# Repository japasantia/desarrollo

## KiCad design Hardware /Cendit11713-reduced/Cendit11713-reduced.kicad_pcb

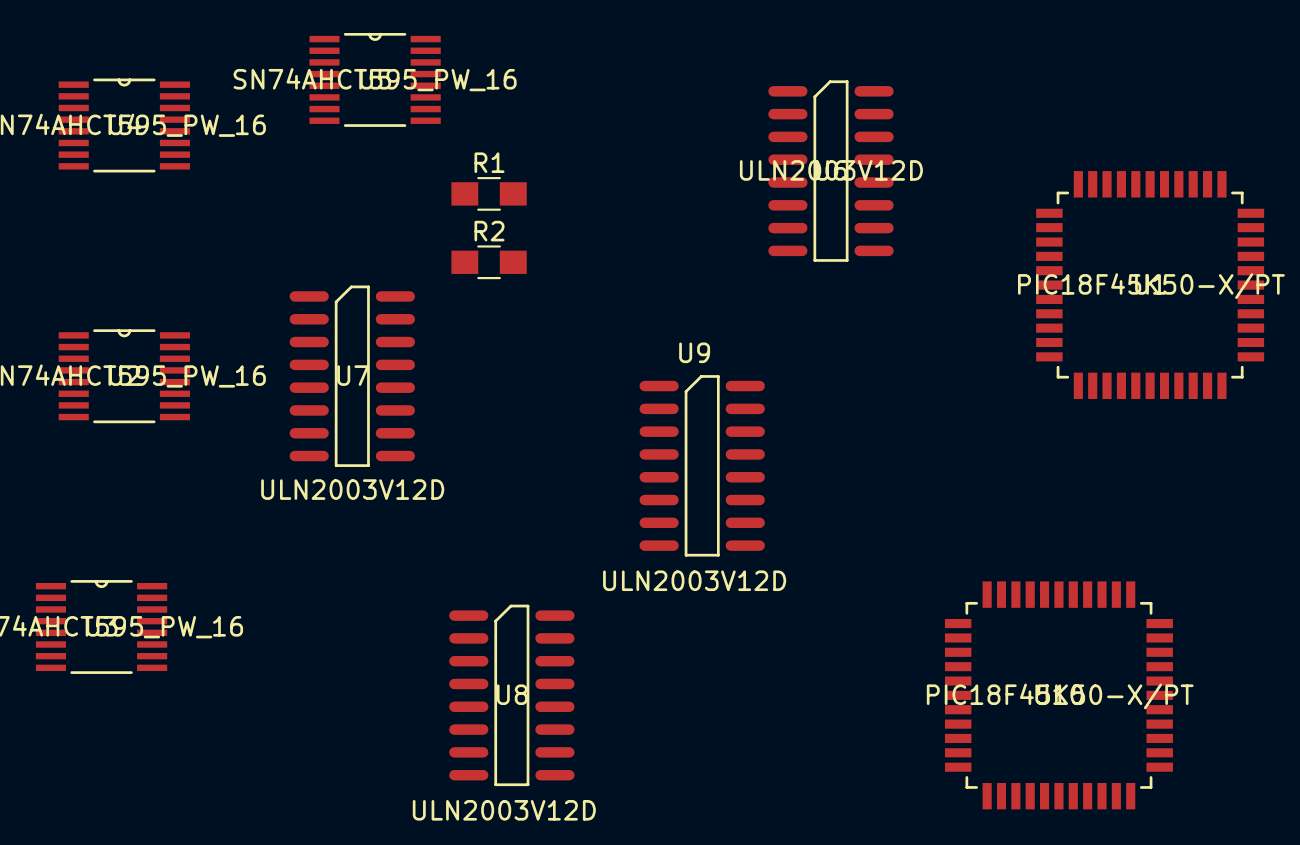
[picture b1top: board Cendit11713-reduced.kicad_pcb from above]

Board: 2 copper layers, 12 parts (0 on the bottom side), 57 nets, no tracks yet.

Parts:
R1, R2: R; R_0805_HandSoldering
U1, U10: PIC18F45K50-X/PT; PIC18F45K50-X_PT
U2, U3, U4, U5: SN74AHCT595_PW_16
U6, U7, U8, U9: ULN2003V12D; ULN2003V12DR

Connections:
+5V: U1.28, U4.16, U5.16, U10.28
/BX0: U4.15, U6.1, U8.1
/BX1: U6.2, U8.2
/BX2: U6.3, U8.3
/BX3: U6.4, U8.4
/BX4: U6.5, U8.5
/BX6: U6.7, U8.7
/BX7: U7.1, U9.1
/BX8: U4.9, U7.2, U9.2
/BX9: U5.15, U7.3, U9.3
/BX10: U5.1, U7.4, U9.4
/BX11: U5.2, U7.5, U9.5
/BX12: U5.3, U7.6, U9.6
/BX13: U5.4, U7.7, U9.7
GND: U1.29, U4.8, U5.8, U6.8, U7.8, U8.8, U9.8, U10.29
unnamed: R1.1, R2.1, U1.41, U10.41
unnamed: R1.2, R2.2, U1.35, U10.35
unnamed: U1.1, U10.1
unnamed: U1.2, U10.2
unnamed: U1.3, U10.3
unnamed: U1.4, U10.4
unnamed: U1.5, U10.5
unnamed: U1.6, U10.6
unnamed: U1.7, U10.7
unnamed: U1.8, U10.8
unnamed: U1.9, U10.9
unnamed: U1.10, U10.10
unnamed: U1.11, U10.11
unnamed: U1.12, U10.12
unnamed: U1.13, U10.13
unnamed: U1.14, U10.14
unnamed: U1.15, U10.15
unnamed: U1.16, U10.16
unnamed: U1.17, U10.17
unnamed: U1.18, U10.18
unnamed: U1.19, U10.19
unnamed: U1.20, U10.20
unnamed: U1.21, U10.21
unnamed: U1.22, U10.22
unnamed: U1.23, U10.23
unnamed: U1.24, U10.24
unnamed: U1.25, U10.25
unnamed: U1.26, U10.26
unnamed: U1.27, U10.27
unnamed: U1.30, U10.30
unnamed: U1.31, U10.31
unnamed: U1.32, U10.32
unnamed: U1.33, U10.33
unnamed: U1.34, U10.34
unnamed: U1.36, U10.36
unnamed: U1.37, U10.37
unnamed: U1.38, U10.38
unnamed: U1.39, U10.39
unnamed: U1.40, U10.40
unnamed: U1.42, U10.42
unnamed: U1.43, U10.43
unnamed: U1.44, U10.44

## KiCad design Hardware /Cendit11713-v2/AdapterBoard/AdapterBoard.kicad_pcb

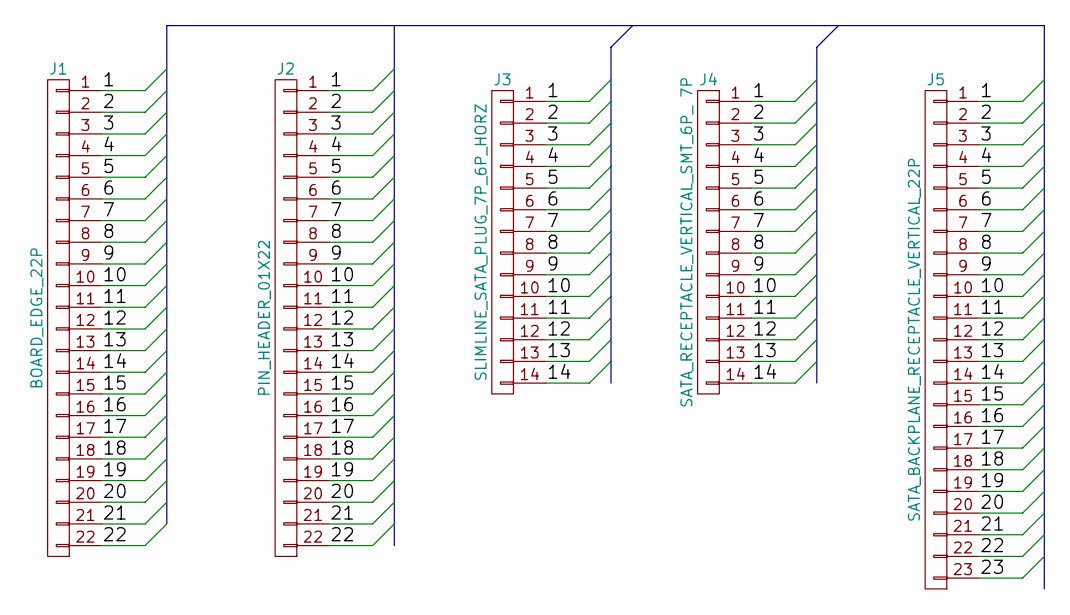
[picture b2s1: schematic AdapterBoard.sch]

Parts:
J1: BOARD_EDGE_22P; CARD_EDGE_22P
J2: PIN_HEADER_01X22; Pin_Header_Straight_1x22_Pitch2.54mm
J3: SLIMLINE_SATA_PLUG_7P_6P_HORZ; SLIMLINE_SATA_PLUG_7P_6P
J4: SATA_RECEPTACLE_VERTICAL_SMT_6P_ 7P; SATA_RECEPTACLE_VERTICAL_SMT_6P_7P
J5: SATA_BACKPLANE_RECEPTACLE_VERTICAL_22P

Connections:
/1: J1.1, J2.1, J3.1, J4.1, J5.1
/2: J1.2, J2.2, J3.2, J4.2, J5.2
/3: J1.3, J2.3, J3.3, J4.3, J5.3
/4: J1.4, J2.4, J3.4, J4.4, J5.4
/5: J1.5, J2.5, J3.5, J4.5, J5.5
/6: J1.6, J2.6, J3.6, J4.6, J5.6
/7: J1.7, J2.7, J3.7, J4.7, J5.7
/8: J1.8, J2.8, J3.8, J4.8, J5.8
/9: J1.9, J2.9, J3.9, J4.9, J5.9
/10: J1.10, J2.10, J3.10, J4.10, J5.10
/11: J1.11, J2.11, J3.11, J4.11, J5.11
/12: J1.12, J2.12, J3.12, J4.12, J5.12
/13: J1.13, J2.13, J3.13, J4.13, J5.13
/14: J1.14, J2.14, J3.14, J4.14, J5.14
/15: J1.15, J2.15, J5.15
/16: J1.16, J2.16, J5.16
/17: J1.17, J2.17, J5.17
/18: J1.18, J2.18, J5.18
/19: J1.19, J2.19, J5.19
/20: J1.20, J2.20, J5.20
/21: J1.21, J2.21, J5.21
/22: J1.22, J2.22, J5.22
GND: J5.23

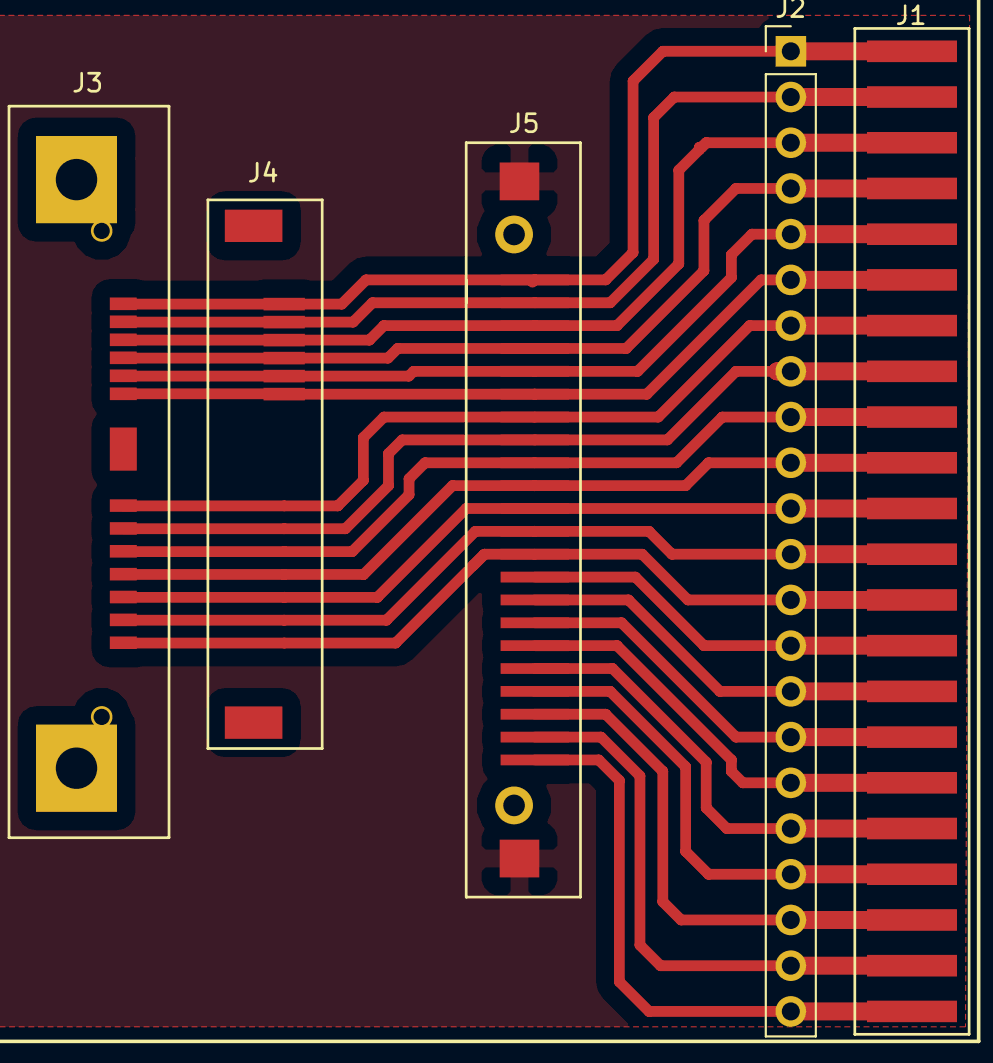
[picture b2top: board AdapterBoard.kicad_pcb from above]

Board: 2 copper layers, 5 parts (0 on the bottom side), 22 nets.

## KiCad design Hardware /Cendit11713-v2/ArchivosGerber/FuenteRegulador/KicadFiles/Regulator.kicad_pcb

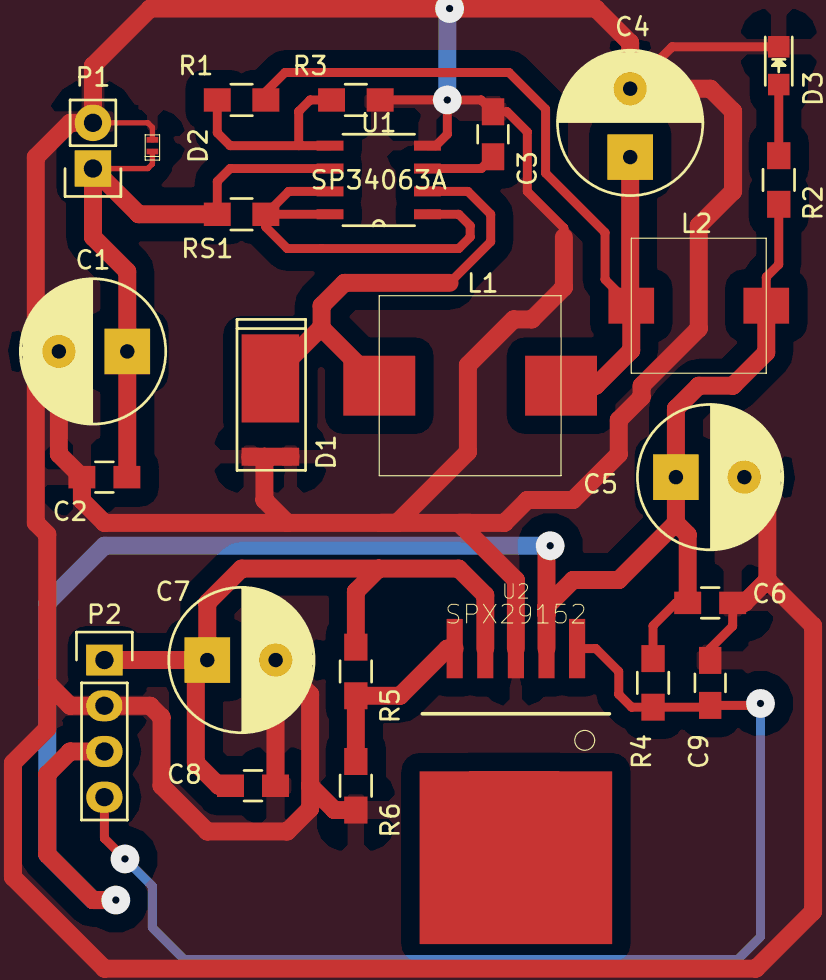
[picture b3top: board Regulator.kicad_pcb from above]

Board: 2 copper layers, 25 parts (0 on the bottom side), 12 nets.

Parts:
C1: 100uF@50V; C_Radial_D8_L13_P3.8
C2, C6, C8: 100nF; C_0805_HandSoldering
C3: 0.3nF; C_0805_HandSoldering
C4: 470uF@10V; C_Radial_D8_L13_P3.8
C5, C7: 100uF@10V; C_Radial_D8_L13_P3.8
C9: 1uF; C_0805_HandSoldering
D1: DST5100S; DST5100S-TO-277B
D2: SPHV24-01ETG; SPHV24-SOD882
D3: LED; LED_0805
L1: 220uH; INDUCTOR_LCM1060
L2: 1uH; INDUCTOR_LKS0745
P1: PWR_IN_2P; Pin_Header_Straight_1x02
P2: PWR_OUT_4P; Pin_Header_Straight_1x04
R1: 2.0k; R_0805_HandSoldering
R2: 330; R_0805_HandSoldering
R3: 1.0k; R_0805_HandSoldering
R4: 10k; R_0805_HandSoldering
R5: 4.3k; R_0805_HandSoldering
R6: 3.0k; R_0805_HandSoldering
RS1: 0.20; R_0805_HandSoldering
U1: SP34063A; SP34063AEN-L&slash_TR
U2: SPX29152; SPX29152T5-TO-263-5

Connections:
/ENABLE: C9.1, P2.4, R4.1, U2.1
/VDC_5.0V: C7.1, C8.1, P2.1, R5.2, U2.4
/VDC_24V: C1.1, C2.1, D2.1, P1.1, RS1.2, U1.6
/VREG: C5.1, C6.1, L2.2, P2.3, R2.1, R4.2, U2.2
GNDPWR: C1.2, C2.2, C3.2, C4.2, C5.2, C6.2, C7.2, C8.2, C9.2, D1.2, D2.2, D3.1, P1.2, P2.2, R3.1, R6.1, U1.4, U2.3
unnamed: C3.1, U1.3
unnamed: C4.1, L1.2, L2.1, R1.1
unnamed: D1.1, L1.1, U1.2
unnamed: D3.2, R2.2
unnamed: R1.2, R3.2, U1.5
unnamed: R5.1, R6.2, U2.5
unnamed: RS1.1, U1.1, U1.7, U1.8

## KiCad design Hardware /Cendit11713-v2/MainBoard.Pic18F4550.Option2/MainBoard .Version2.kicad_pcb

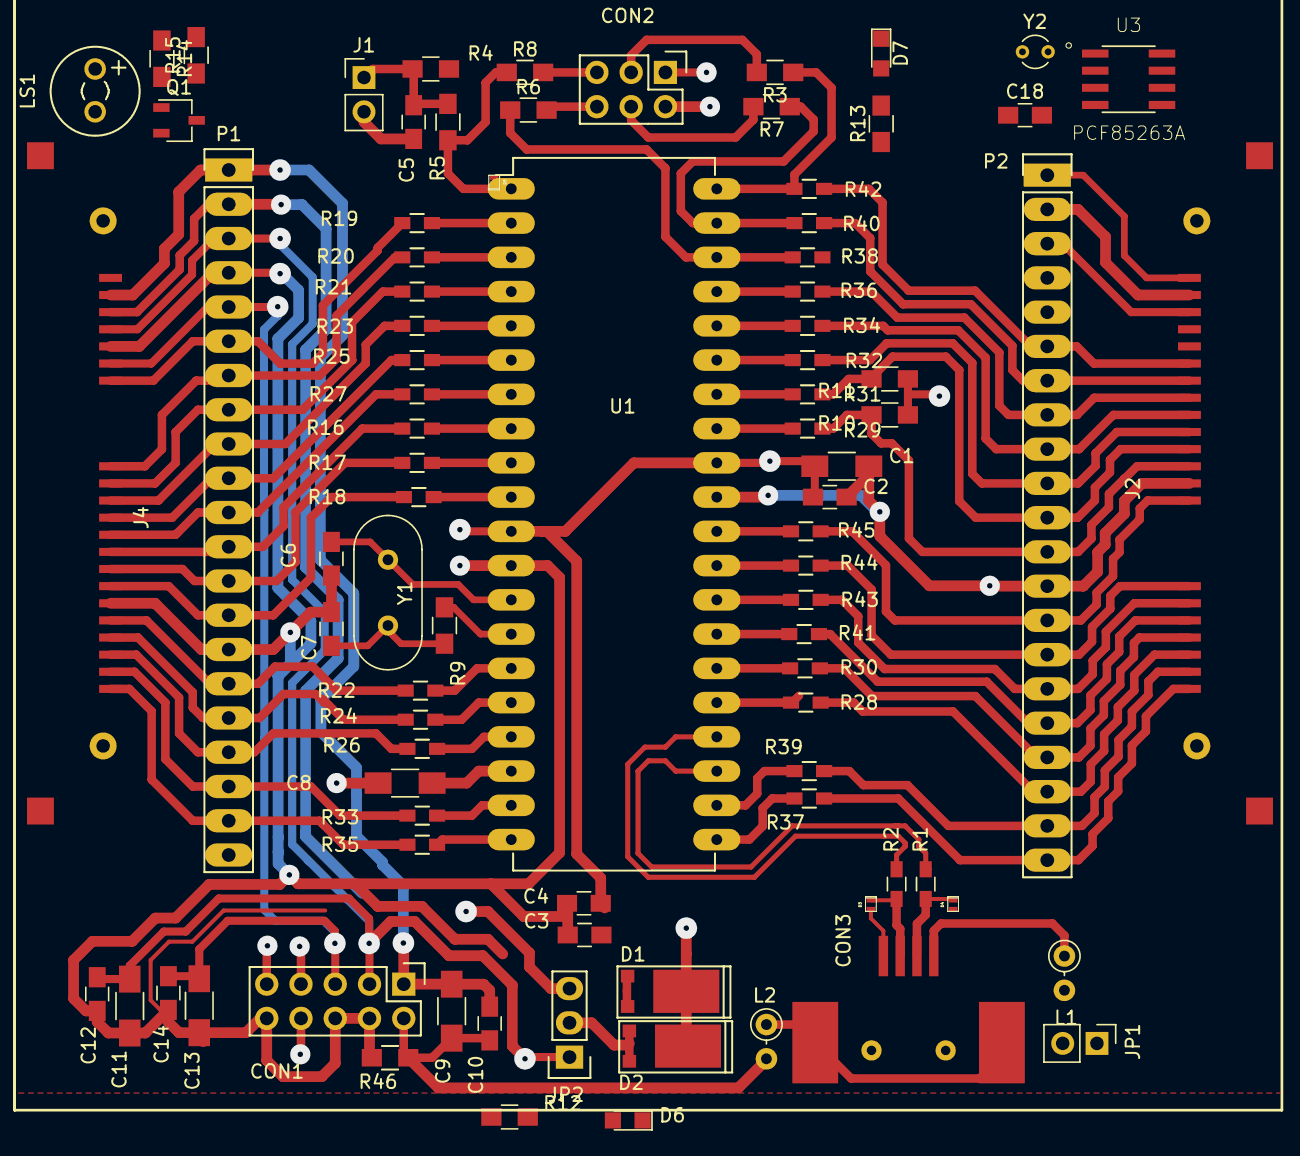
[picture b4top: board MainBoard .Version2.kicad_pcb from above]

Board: 2 copper layers, 86 parts (0 on the bottom side), 92 nets.

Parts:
C1, C8, C9, C11, C13: 1uF; C_1206_HandSoldering
C2, C3, C4, C5, C10, C12, C14, C18: 0.1uF; C_0805_HandSoldering
C6, C7: 22p; C_0805_HandSoldering
CON1: POWER_BUS; Pin_Header_Straight_2x05
CON2: ICSP_CON; Pin_Header_Straight_2x03
CON3: USB_CON; USB_SMT_B
D1, D2: DST5100S; DST5100S-TO-277B
D3, D4, D5: SP1003-01ETG
D6, D7: LED; LED_0805
J1: RESET_CON; Pin_Header_Straight_1x02_Pitch2.54mm
J2, J4: SATA_PLUG _22P_SMT; SATA_PLUG_22P_SMT
JP1: JMP_USB_VBUS; Pin_Header_Straight_1x02_Pitch2.54mm
JP2: JMP_3V_5V; Pin_Header_Straight_1x03
L1, L2: FERRITE_BEAD; L_Axial_L5.3mm_D2.2mm_P2.54mm_Vertical_Vishay_IM-1
LS1: Speaker_Crystal; MagneticBuzzer_Kingstate_KCG0601
P1, P2: DEBUG_HEADER_21P; DEBUG_PIN_HEADER_21P
Q1: 2N2222; TSOT-23
R1, R2: 33; R_0603_HandSoldering
R3, R5, R6, R7: 100R; R_0805_HandSoldering
R4: 4,7K; R_0805_HandSoldering
R8: 100; R_0805_HandSoldering
R9: RS; R_0805_HandSoldering
R10, R11: 4.7K; R_0805_HandSoldering
R12, R13, R14: 300; R_0805_HandSoldering
R15: 1k; R_0805_HandSoldering
R16, R17, R18, R19, R20, R21, R22, R23, R24, R25, R26, R27, R28, R29, R30, R31, R32, R33, R34, R35, R36, R37, R38, R39, R40, R41, R42, R43, R44, R45: RP; R_0603_HandSoldering
R46: 0; R_0805_HandSoldering
U1: PIC18F4550-I/P; PIC18F4550-PDIP
U3: PCF85263A; PCF85263A_SO8
Y1: Crystal; Crystal_HC49-4H_Vertical
Y2: 32.768KHZ; Crystal_C26-LF_d2.1mm_l6.5mm_Vertical

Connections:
//CS_LAN: J2.7, P2.15, R44.1
//CS_VIKING: J2.8, P2.14, R45.1
//RST_GPIB: J2.2, P2.20, R39.1
//RST_KEY: J2.1, P2.21, R37.1
//RST_LAN: J2.5, P2.17, R41.1
//RST_VIKING: J2.6, P2.16, R43.1
/D+: CON3.3, D3.1, R2.2
/D-: CON3.2, D4.1, R1.2
/GND_PWR: J2.20, P2.2
/LVP: R6.1, R38.1, U1.38
/MCLR_INT: D5.1, R5.1, R8.1, U1.1
/MISO: J2.3, P2.19, R28.1
/MOSI: J2.4, P2.18, R30.1
/OSC1: C6.1, U1.13, Y1.2
/OSC2: R9.1, U1.14
/PA0: J4.7, P1.6, R14.2, R19.2
/PA1: J4.8, P1.7, R20.2
/PA2: J4.9, P1.8, R21.2
/PA3: J4.10, P1.9, R23.2
/PA4: J4.11, P1.10, R25.2
/PA5: J4.12, P1.11, R27.2
/PB0: J2.10, P2.12, R10.2, R29.2, U3.5
/PB1: J2.11, P2.11, R11.2, R31.2, U3.6
/PB2: J2.12, P2.10, R32.2
/PB3: J2.13, P2.9, R34.2
/PB4: J2.14, P2.8, R13.1, R36.2
/PB6: J2.15, P2.7, R40.2
/PB7: J2.16, P2.6, R42.2
/PC0: J4.17, P1.16, R22.1
/PC1: J4.18, P1.17, R24.1
/PC2: J4.19, P1.18, R26.1
/PD0: J4.20, P1.19, R33.1
/PD1: J4.21, P1.20, R35.1
/PE0: J4.13, P1.12, R16.1
/PE1: J4.14, P1.13, R17.1
/PE2: J4.15, P1.14, R18.1
/PGC: R7.1, R40.1, U1.39
/PGD: R3.1, R42.1, U1.40
/RA0: R19.1, U1.2
/RA1: R20.1, U1.3
/RA2: R21.1, U1.4
/RA3: R23.1, U1.5
/RA4: R25.1, U1.6
/RA5: R27.1, U1.7
/RB0: R29.1, U1.33
/RB1: R31.1, U1.34
/RB2: R32.1, U1.35
/RB3: R34.1, U1.36
/RB4: R36.1, U1.37
/RC0: R22.2, U1.15
/RC1: R24.2, U1.16
/RC2: R26.2, U1.17
/RC6: R28.2, U1.25
/RC7: R30.2, U1.26
/RD0: R33.2, U1.19
/RD1: R35.2, U1.20
/RD2: R37.2, U1.21
/RD3: R39.2, U1.22
/RD4: R41.2, U1.27
/RD5: R43.2, U1.28
/RD6: R44.2, U1.29
/RD7: R45.2, U1.30
/RE0: R16.2, U1.8
/RE1: R17.2, U1.9
/RE2: R18.2, U1.10
/USB_D+: R2.1, U1.24
/USB_D-: R1.1, U1.23
/USB_VBUS: JP1.1, L1.2
/VCC_5V: C11.1, C12.1, CON1.3, J2.19, J4.4, JP2.1, P1.3, P2.3
/VDD_3V: C13.1, C14.1, C18.1, CON1.5, J4.6, JP2.3, P1.5, P2.5, U3.8
/VPWR: C9.1, C10.1, CON1.1, J2.21, J4.2, P1.1, P2.1
/VUSB_CAP: C8.2, U1.18
GNDD: C1.2, C2.2, C3.2, C4.2, C5.2, C6.2, C7.2, C8.1, C11.2, C12.2, C13.2, C14.2, C18.2, CON1.4, CON1.6, CON1.10, CON2.2, CON3.4, D3.2, D4.2, D5.2, D6.1, D7.1, J1.2, J2.9, J2.18, J4.5, J4.16, P1.4, P1.15, P2.4, P2.13, Q1.3, R46.1, U1.12, U1.31, U3.4
GNDPWR: C9.2, C10.2, CON1.2, J4.3, L2.2, P1.2, R46.2
unnamed: C5.1, J1.1, R4.2, R5.2
unnamed: C7.1, R9.2, Y1.1
unnamed: CON2.3, R3.2
unnamed: CON2.4, R7.2
unnamed: CON2.5, R8.2
unnamed: CON2.6, R6.2
unnamed: CON3.1, L1.1
unnamed: CON3.5, L2.1
unnamed: D1.2, JP1.2
unnamed: D2.2, JP2.2
unnamed: D6.2, R12.2
unnamed: D7.2, R13.2
unnamed: LS1.1, R15.1
unnamed: LS1.2, Q1.2
unnamed: Q1.1, R14.1
unnamed: U3.1, Y2.1
unnamed: U3.2, Y2.2
VDD: C1.1, C2.1, C3.1, C4.1, CON2.1, D1.1, D2.1, R4.1, R10.1, R11.1, R12.1, R15.2, U1.11, U1.32

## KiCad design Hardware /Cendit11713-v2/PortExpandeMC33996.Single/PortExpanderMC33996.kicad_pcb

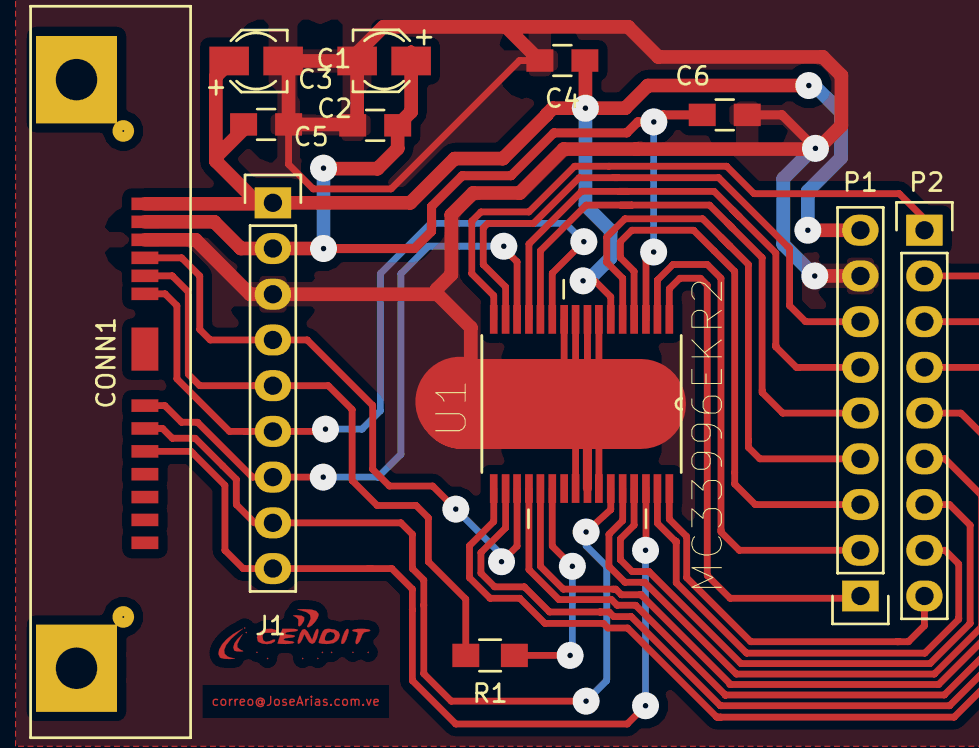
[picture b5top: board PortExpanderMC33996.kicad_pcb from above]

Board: 2 copper layers, 13 parts (0 on the bottom side), 26 nets.

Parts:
C1, C3: 10uF; c_elec_3x5.3
C2, C4, C5, C6: 0.1uF; C_0805_HandSoldering
CONN1: VIKING_SPI_BUS; SLIMLINE_SATA_PLUG_7P_6P
G1: LOGO; CENDIT_LOGO_SOLDER
J1: DEBUG_CONN; Pin_Header_Straight_1x09
P1, P2: VIKING_HEADER_9P; Pin_Header_Straight_1x09
R1: RL; R_0805_HandSoldering
U1: MC33996EKR2

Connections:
//CS: CONN1.7, J1.7, U1.14
//RESET: CONN1.8, J1.8, U1.27
/MISO: CONN1.5, J1.5, R1.2
/MOSI: CONN1.4, J1.4, U1.19
/P0: P1.1, U1.1
/P1: P1.2, U1.2
/P2: P1.3, U1.4
/P3: P1.4, U1.5
/P4: P1.5, U1.12
/P5: P1.6, U1.13
/P6: P1.7, U1.15
/P7: P2.1, U1.16
/P8: P2.2, U1.17
/P9: P2.3, U1.18
/P10: P2.4, U1.20
/P11: P2.5, U1.21
/P12: P2.6, U1.28
/P13: P2.7, U1.29
/P14: P2.8, U1.31
/P15: P2.9, U1.32
/PWM: CONN1.9, J1.9, U1.30
/SCLK: CONN1.6, J1.6, U1.11
GNDPWR: C1.2, C2.2, C3.2, C4.2, C5.2, C6.2, CONN1.3, J1.3, P1.8, U1.7, U1.8, U1.9, U1.10, U1.24, U1.25, U1.26, U1.33
unnamed: R1.1, U1.22
VCC: C3.1, C5.1, C6.1, CONN1.2, J1.2, U1.3
VPP: C1.1, C2.1, C4.1, CONN1.1, J1.1, P1.9, U1.6

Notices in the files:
parts and their libraries:
Copyright 2016 Accelerated Designs. All rights reserved.
